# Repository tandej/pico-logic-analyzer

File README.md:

# pico-logic-analyzer

## Auto-generated content

[schematic (pdf)](https://raw.githubusercontent.com/tandej/pico-logic-analyzer/main-generated-output/sch.pdf)

[gerber files (zip)](https://raw.githubusercontent.com/tandej/pico-logic-analyzer/main-generated-output/gerbers.zip)

[board 3d model (step)](https://raw.githubusercontent.com/tandej/pico-logic-analyzer/main-generated-output/board-model.step)

[bill of materials (csv)](https://raw.githubusercontent.com/tandej/pico-logic-analyzer/main-generated-output/bom.csv)

[assembly pos file (csv)](https://raw.githubusercontent.com/tandej/pico-logic-analyzer/main-generated-output/pos-all-pos.csv)

[design rules check output](https://raw.githubusercontent.com/tandej/pico-logic-analyzer/main-generated-output/drc-output.txt)

[electrical rules check output](https://raw.githubusercontent.com/tandej/pico-logic-analyzer/main-generated-output/erc-output.txt)

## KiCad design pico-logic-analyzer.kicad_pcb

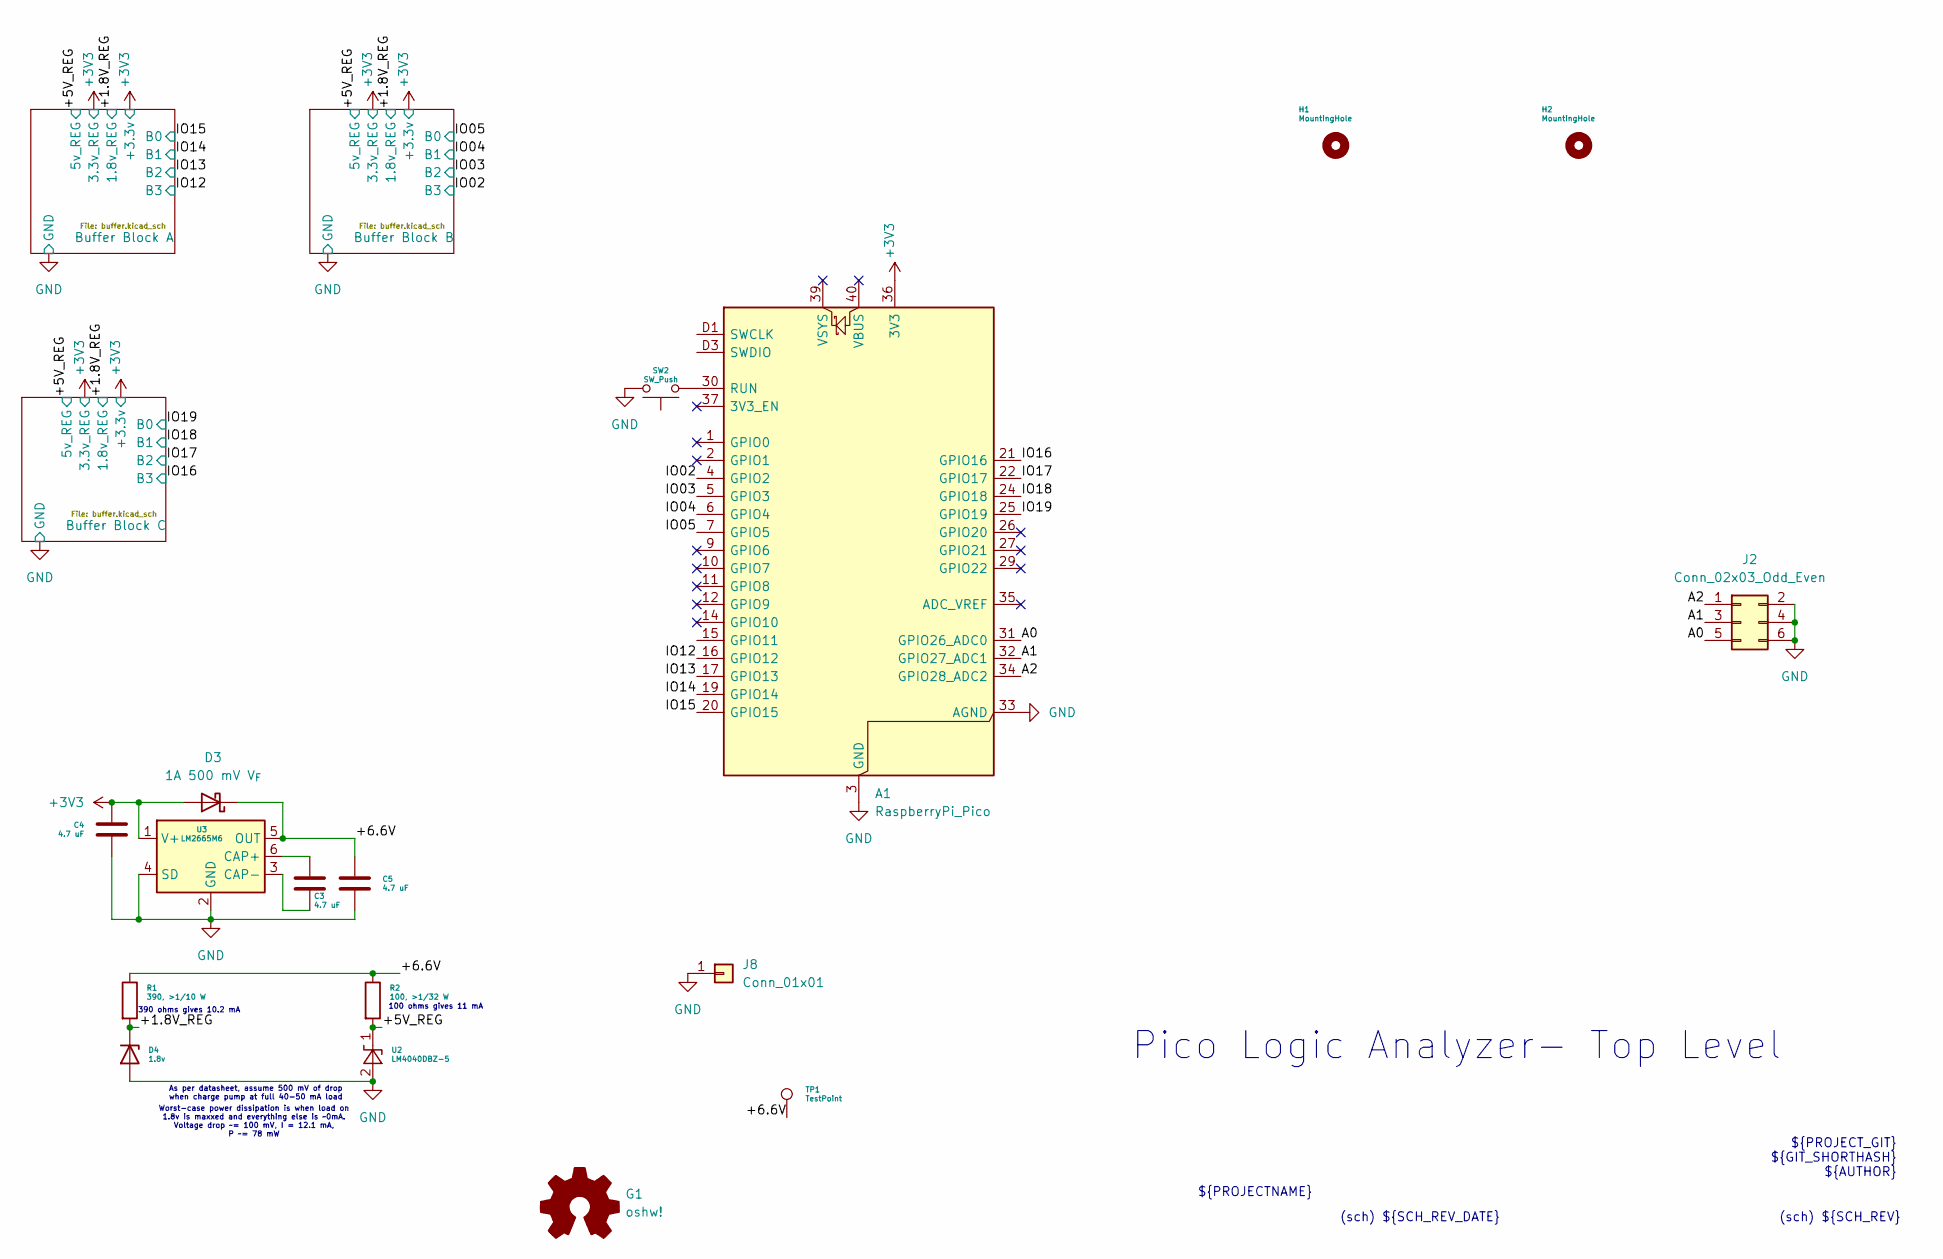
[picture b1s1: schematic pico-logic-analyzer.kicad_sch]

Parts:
A1: RaspberryPi_Pico; RaspberryPi_Pico_SMD
C3, C4, C5: 4.7 uF; C_0603_1608Metric
D3: 1A 500 mV V_{F}; D_SOD-123F
D4: 1.8v; D_SOD-123
G1: oshw!; OSHW-Logo2_7.3x6mm_SilkScreen
H1, H2: MountingHole; MountingHole_3.2mm_M3
J2: Conn_02x03_Odd_Even; PinSocket_2x03_P2.54mm_Horizontal
J8: Conn_01x01; PinHeader_1x01_P2.54mm_Vertical
R1: 390, >1/10 W; R_0402_1005Metric
R2: 100, >1/32 W; R_0402_1005Metric
SW2: SW_Push; SW_Tactile_SPST_NO_Straight_CK_PTS636Sx25SMTRLFS
TP1: TestPoint; TestPoint_Pad_D1.5mm
U2: LM4040DBZ-5; SOT-23
U3: LM2665M6; SOT-23-6

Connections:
+3V3: A1.36 (3V3), C4.2, D3.2 (A), U3.1 (V+); also elsewhere on the board
/+1.8V_REG: D4.1 (K), R1.2; also elsewhere on the board
/+5V_REG: R2.2, U2.1 (K); also elsewhere on the board
/+6.6V: C5.2, D3.1 (K), R1.1, R2.1, TP1.1, U3.5 (OUT)
/A0: A1.31 (GPIO26_ADC0), J2.5
/A1: A1.32 (GPIO27_ADC1), J2.3
/A2: A1.34 (GPIO28_ADC2), J2.1
/IO02: A1.4 (GPIO2); also elsewhere on the board
/IO03: A1.5 (GPIO3); also elsewhere on the board
/IO04: A1.6 (GPIO4); also elsewhere on the board
/IO05: A1.7 (GPIO5); also elsewhere on the board
/IO12: A1.16 (GPIO12); also elsewhere on the board
/IO13: A1.17 (GPIO13); also elsewhere on the board
/IO14: A1.19 (GPIO14); also elsewhere on the board
/IO15: A1.20 (GPIO15); also elsewhere on the board
/IO16: A1.21 (GPIO16); also elsewhere on the board
/IO17: A1.22 (GPIO17); also elsewhere on the board
/IO18: A1.24 (GPIO18); also elsewhere on the board
/IO19: A1.25 (GPIO19); also elsewhere on the board
GND: A1.3 (GND), A1.8 (GND), A1.13 (GND), A1.18 (GND), A1.23 (GND), A1.28 (GND), A1.33 (AGND), A1.38 (GND), A1.D2 (GND), C4.1, C5.1, D4.2 (A), J2.2, J2.4, J2.6, J8.1, SW2.2, U2.2 (A), U3.2 (GND), U3.4 (SD); also elsewhere on the board
unnamed: A1.30 (RUN), SW2.1
unnamed: C3.2, U3.6 (CAP+)
unnamed: C3.1, U3.3 (CAP-)

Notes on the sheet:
${PROJECTNAME}
(sch) ${SCH_REV_DATE}
Worst-case power dissipation is when load on 1.8v is maxxed and everything else is ~0mA. Voltage drop ~= 100 mV, I = 12.1 mA, P ~= 78 mW
(sch) ${SCH_REV}
390 ohms gives 10.2 mA
${PROJECT_GIT} ${GIT_SHORTHASH} ${AUTHOR}
Pico Logic Analyzer- Top Level
100 ohms gives 11 mA
As per datasheet, assume 500 mV of drop when charge pump at full 40-50 mA load

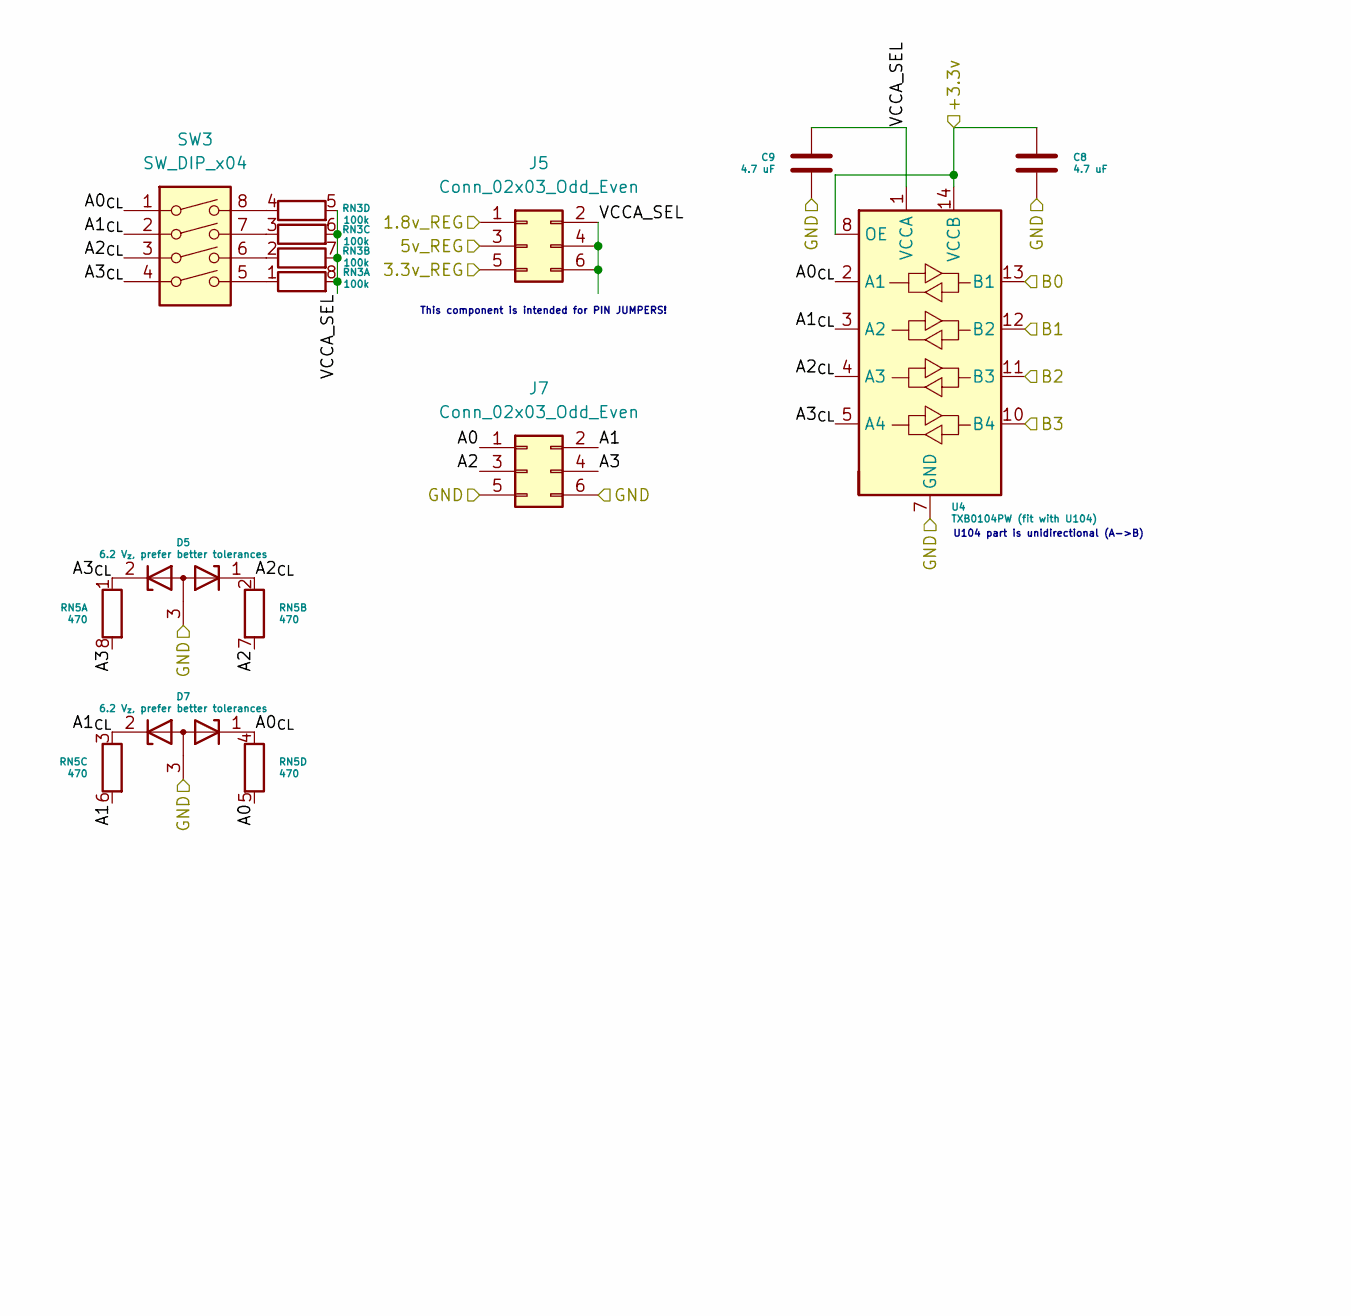
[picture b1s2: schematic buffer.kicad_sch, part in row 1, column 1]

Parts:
C8, C9: 4.7 uF; C_0603_1608Metric
D5, D7: 6.2 V_{z}, prefer better tolerances; SOT-23
J5: Conn_02x03_Odd_Even; PinHeader_2x03_P2.54mm_Vertical
J7: Conn_02x03_Odd_Even; PinSocket_2x03_P2.54mm_Horizontal
RN3: 100k; R_Array_Convex_4x0402
RN5: 470; R_Array_Convex_4x0402
SW3: SW_DIP_x04; SW_DIP_SPSTx04_Slide_9.78x12.34mm_W7.62mm_P2.54mm
U4: TXB0104PW (fit with U104); TSSOP-14_4.4x5mm_P0.65mm

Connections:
+3V3: C8.2, J5.5, U4.8 (OE), U4.14 (VCCB); also elsewhere on the board
/+1.8V_REG: J5.1; also elsewhere on the board
/+5V_REG: J5.3; also elsewhere on the board
/Buffer Block A/A0: J7.1, RN5.5 (R4.2)
/Buffer Block A/A0_{CL}: D7.1 (K), RN5.4 (R4.1), SW3.1, U4.2 (A1)
/Buffer Block A/A1: J7.2, RN5.6 (R3.2)
/Buffer Block A/A1_{CL}: D7.2 (K), RN5.3 (R3.1), SW3.2, U4.3 (A2)
/Buffer Block A/A2: J7.3, RN5.7 (rR2.2)
/Buffer Block A/A2_{CL}: D5.1 (K), RN5.2 (R2.1), SW3.3, U4.4 (A3)
/Buffer Block A/A3: J7.4, RN5.8 (R1.2)
/Buffer Block A/A3_{CL}: D5.2 (K), RN5.1 (R1.1), SW3.4, U4.5 (A4)
/Buffer Block A/VCCA_SEL: C9.2, J5.2, J5.4, J5.6, RN3.5 (R4.2), RN3.6 (R3.2), RN3.7 (R2.2), RN3.8 (R1.2), U4.1 (VCCA)
/IO12: U4.10 (B4); also elsewhere on the board
/IO13: U4.11 (B3); also elsewhere on the board
/IO14: U4.12 (B2); also elsewhere on the board
/IO15: U4.13 (B1); also elsewhere on the board
GND: C8.1, C9.1, D5.3 (A), D7.3 (A), J7.5, J7.6, U4.7 (GND); also elsewhere on the board
unnamed: RN3.1 (R1.1), SW3.5
unnamed: RN3.2 (R2.1), SW3.6
unnamed: RN3.3 (R3.1), SW3.7
unnamed: RN3.4 (R4.1), SW3.8

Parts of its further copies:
C1, C2, C6, C7: 4.7 uF; C_0603_1608Metric
D1, D2, D6, D8: 6.2 V_{z}, prefer better tolerances; SOT-23
J1, J6: Conn_02x03_Odd_Even; PinHeader_2x03_P2.54mm_Vertical
J3, J4: Conn_02x03_Odd_Even; PinSocket_2x03_P2.54mm_Horizontal
RN1, RN6: 100k; R_Array_Convex_4x0402
RN2, RN4: 470; R_Array_Convex_4x0402
SW1, SW4: SW_DIP_x04; SW_DIP_SPSTx04_Slide_9.78x12.34mm_W7.62mm_P2.54mm
U1, U5: TXB0104PW (fit with U104); TSSOP-14_4.4x5mm_P0.65mm

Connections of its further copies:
+3V3: C1.2, C7.2, J1.5, J6.5, U1.8 (OE), U1.14 (VCCB), U5.8 (OE), U5.14 (VCCB); also elsewhere on the board
/+1.8V_REG: J1.1, J6.1; also elsewhere on the board
/+5V_REG: J1.3, J6.3; also elsewhere on the board
/Buffer Block B/A0: J3.1, RN2.5 (R4.2)
/Buffer Block B/A0_{CL}: D2.1 (K), RN2.4 (R4.1), SW1.1, U1.2 (A1)
/Buffer Block B/A1: J3.2, RN2.6 (R3.2)
/Buffer Block B/A1_{CL}: D2.2 (K), RN2.3 (R3.1), SW1.2, U1.3 (A2)
/Buffer Block B/A2: J3.3, RN2.7 (rR2.2)
/Buffer Block B/A2_{CL}: D1.1 (K), RN2.2 (R2.1), SW1.3, U1.4 (A3)
/Buffer Block B/A3: J3.4, RN2.8 (R1.2)
/Buffer Block B/A3_{CL}: D1.2 (K), RN2.1 (R1.1), SW1.4, U1.5 (A4)
/Buffer Block B/VCCA_SEL: C2.2, J1.2, J1.4, J1.6, RN1.5 (R4.2), RN1.6 (R3.2), RN1.7 (R2.2), RN1.8 (R1.2), U1.1 (VCCA)
/Buffer Block C/A0: J4.1, RN4.5 (R4.2)
/Buffer Block C/A0_{CL}: D6.1 (K), RN4.4 (R4.1), SW4.1, U5.2 (A1)
/Buffer Block C/A1: J4.2, RN4.6 (R3.2)
/Buffer Block C/A1_{CL}: D6.2 (K), RN4.3 (R3.1), SW4.2, U5.3 (A2)
/Buffer Block C/A2: J4.3, RN4.7 (rR2.2)
/Buffer Block C/A2_{CL}: D8.1 (K), RN4.2 (R2.1), SW4.3, U5.4 (A3)
/Buffer Block C/A3: J4.4, RN4.8 (R1.2)
/Buffer Block C/A3_{CL}: D8.2 (K), RN4.1 (R1.1), SW4.4, U5.5 (A4)
/Buffer Block C/VCCA_SEL: C6.2, J6.2, J6.4, J6.6, RN6.5 (R4.2), RN6.6 (R3.2), RN6.7 (R2.2), RN6.8 (R1.2), U5.1 (VCCA)
/IO02: U1.10 (B4); also elsewhere on the board
/IO03: U1.11 (B3); also elsewhere on the board
/IO04: U1.12 (B2); also elsewhere on the board
/IO05: U1.13 (B1); also elsewhere on the board
/IO16: U5.10 (B4); also elsewhere on the board
/IO17: U5.11 (B3); also elsewhere on the board
/IO18: U5.12 (B2); also elsewhere on the board
/IO19: U5.13 (B1); also elsewhere on the board
GND: C1.1, C2.1, C6.1, C7.1, D1.3 (A), D2.3 (A), D6.3 (A), D8.3 (A), J3.5, J3.6, J4.5, J4.6, U1.7 (GND), U5.7 (GND); also elsewhere on the board
unnamed: RN1.1 (R1.1), SW1.5
unnamed: RN1.2 (R2.1), SW1.6
unnamed: RN1.3 (R3.1), SW1.7
unnamed: RN1.4 (R4.1), SW1.8
unnamed: RN6.1 (R1.1), SW4.5
unnamed: RN6.2 (R2.1), SW4.6
unnamed: RN6.3 (R3.1), SW4.7
unnamed: RN6.4 (R4.1), SW4.8

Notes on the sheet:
${PROJECTNAME}
${PROJECT_GIT} ${GIT_SHORTHASH} ${AUTHOR}
(sch) ${SCH_REV}
(sch) ${SCH_REV_DATE}
This component is intended for PIN JUMPERS!
Pico Logic Analyzer- Digital Block
U104 part is unidirectional (A->B)

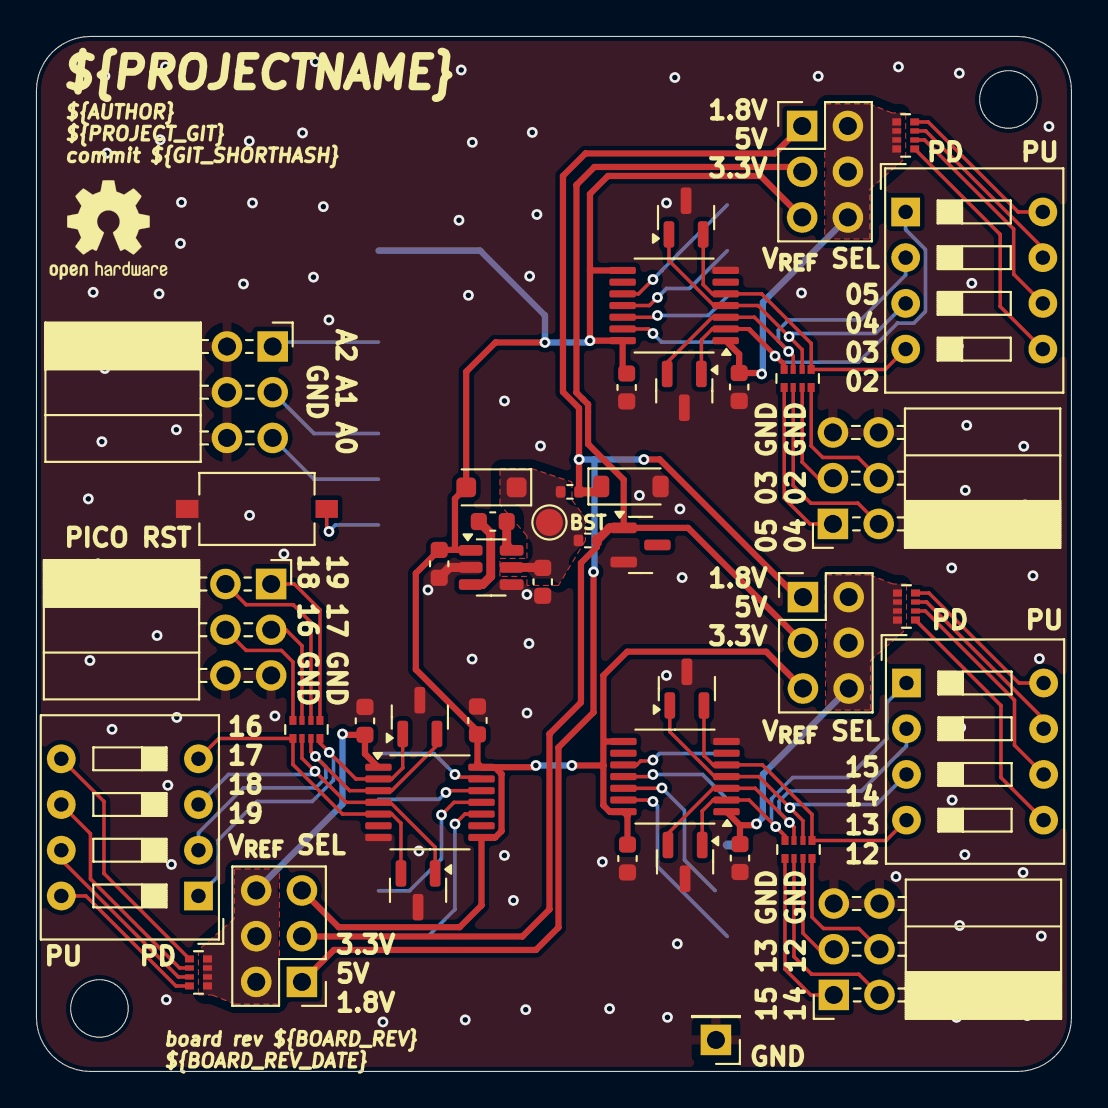
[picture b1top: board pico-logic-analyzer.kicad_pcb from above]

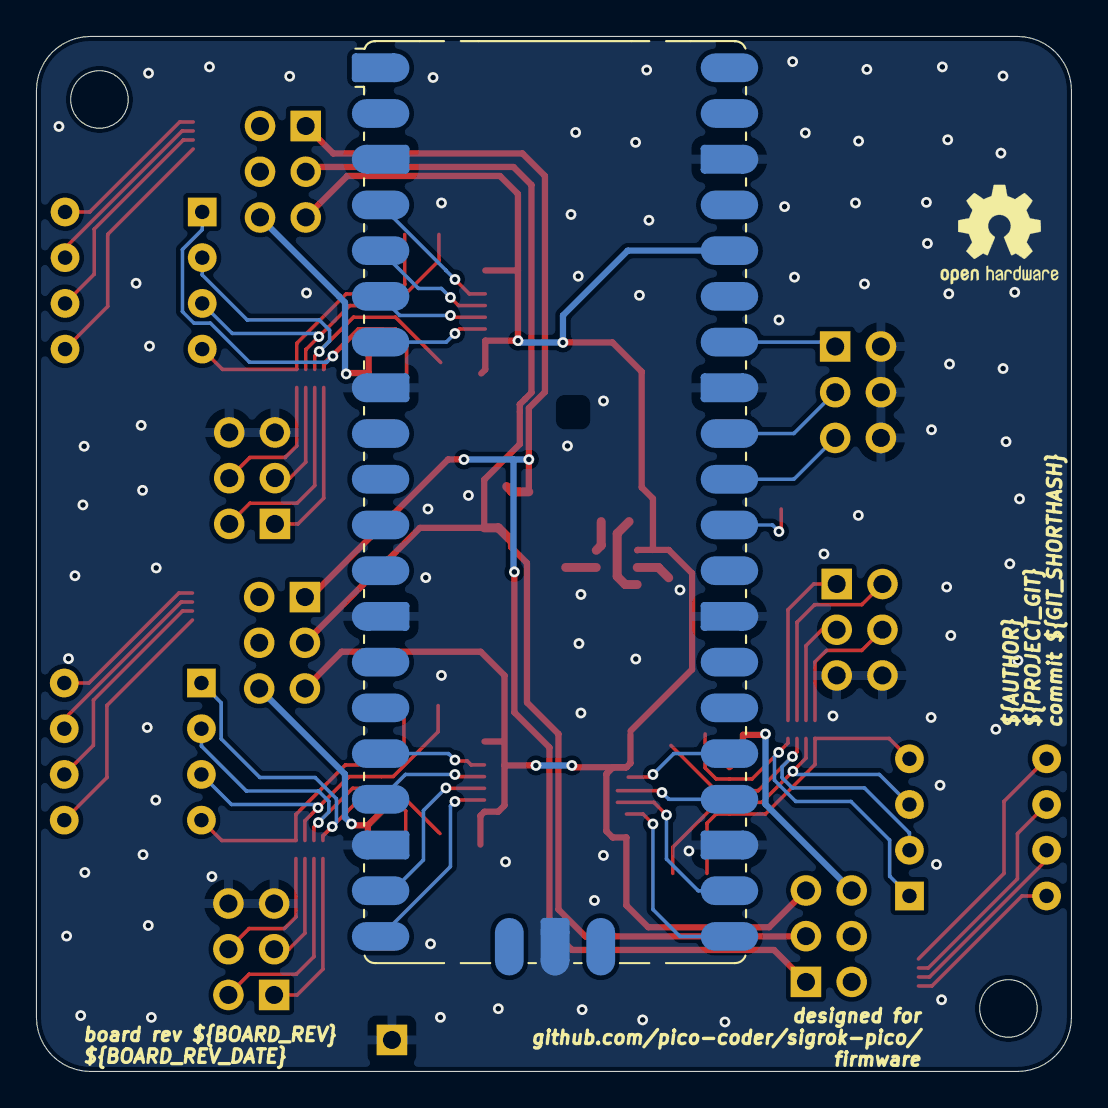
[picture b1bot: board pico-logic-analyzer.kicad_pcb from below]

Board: 4 copper layers, 57.5 x 57.5 mm, 48 parts (2 on the bottom side), 62 nets.

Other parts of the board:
G1#2: oshw!; OSHW-Logo2_7.3x6mm_SilkScreen

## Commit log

2024-11-29 initial commit for CI export testing
2024-11-29 added export script
2024-11-30 silkscreen cleanups
2024-12-01 update templating to do date and user-defined version number instead of trying to make commit hash work
    also, will need to revisit the timestamps that are being generated on otherwise identical gerbers
2024-12-24 2.0 first commit * started switching caps to standard value of 0603 4.7uF (which is overkill everywhere) * tidied up some silkscreen * replaced 4x100kOhm pullup resistors with 1 array (of the same va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
2024-12-24 actually run export scripts
2024-12-27 add zener diode clamping circuit
2025-01-27 remove 3.3v zener from sch - start to switch to stdlib rpi pico -
2025-01-28 layout overhaul backside pico now, which significantly reduces the size of the board and lets me do less suspect routing need to finish power delivery network for 3.3v, 5v reference, and 1.8v referen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
2025-02-02 finish power routing also 9.0 import! jobsets coming soon
    export is very broken at this point, do not trust the artifacts
2025-02-17 backup commit before project structure overhaul
2025-02-18 new project structure
2025-02-18 Update main-generated-output to output generated at ae2b8a3
